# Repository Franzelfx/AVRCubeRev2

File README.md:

# AVR-Cube (Rev2)

**A coin-cell powered electronic dice and two-axis spirit level on an ATtiny24 — seven LEDs, one button, one accelerometer, and a bit-banged I²C bus that shares its pins with the ISP header.**

Shake it and it rolls a number; press the button and the same seven LEDs become a bubble level that follows the tilt of the board. It sleeps after a minute of stillness and wakes on the button, so a CR2032 lasts a long time. Designed as an easy, satisfying through-hole soldering kit: 25 parts, all on one side.

https://user-images.githubusercontent.com/38862049/217531555-265ecb9a-27d7-4d04-bca4-034f5620d8f7.mov

---

## Contents

- [How it works](#how-it-works)
- [Hardware](#hardware)
- [Firmware](#firmware)
- [Building and flashing](#building-and-flashing)
- [Repository layout](#repository-layout)
- [Status and known limitations](#status-and-known-limitations)
- [Author](#author)
- [License](#license)

---

## How it works

The whole device is one state machine driven by two interrupts: a 1 ms timer tick that counts idle time, and the button on `INT0`.

```mermaid
stateDiagram-v2
    [*] --> Calibrate : battery inserted / wake from sleep
    Calibrate --> SpiritLevel : all LEDs → "1" → sensor check ✓ → "2" → offset averaged → ✓
    Calibrate --> Sleep : sensor not answering (✗ shown for 60 s)

    SpiritLevel --> Dice : button
    Dice --> SpiritLevel : button

    state Dice {
        [*] --> Waiting
        Waiting --> Rolling : tilt changes by > 25°
        Rolling --> Waiting : 5 fast + 5 slowing steps, last number stays lit
    }

    SpiritLevel --> Sleep : 60 s without motion
    Dice --> Sleep : 60 s without motion
    SpiritLevel --> Sleep : button held 3 s
    Dice --> Sleep : button held 3 s
    Sleep --> Calibrate : button
```

**Calibration** runs on every wake-up: it lights all LEDs (a visual LED test), reads the accelerometer's `WHO_AM_I` register over I²C, and averages ten samples to get the resting offset on each axis. That offset is what makes the spirit level read "flat" wherever the board happens to sit when powered on — there is no absolute calibration.

**Spirit level** reads X/Y/Z acceleration, subtracts the offset, and converts the X and Y components into roll and pitch angles with `atan(axis / z_offset)`. Within ±1° of level only the centre LED is lit; otherwise the LEDs on the side that is *down* light up — a whole edge if the tilt is along one axis, a single corner if it's diagonal.

**Dice** waits until the angle changes by more than 25° between two readings (a shake or a tilt), then rolls: five numbers at 100 ms, then five more with the delay growing by 100 ms each step, so the animation visibly slows down and settles. The random generator is seeded from the millisecond counter, so the result depends on exactly when you shook it.

**Sleep** puts the accelerometer in standby, switches every I/O pin to input, and enters `SLEEP_MODE_PWR_DOWN` — a few µA. Holding the button lights the LEDs 1…6 as a countdown; at 3 s it sleeps immediately.

## Hardware

| | |
|---|---|
| MCU | Microchip **ATtiny24** (DIP-14, 2 KB flash) at 8 MHz internal RC — the ATtiny84 is a drop-in alternative with more flash |
| Sensor | NXP **MMA8653FC** 3-axis accelerometer (DFN-10), I²C address `0x1D`, ±2 g, 8-bit fast-read mode |
| Display | 7 × 5 mm LEDs in the classic dice pattern, 100 Ω series resistors |
| Input | 6 mm tactile switch on `INT0` |
| Power | CR2032 in a Keystone 106 holder, 3 V direct — no regulator |
| Programming | 2×3 ISP header; the same pins carry the sensor's I²C bus |
| Board | 2-layer, single-sided assembly, KiCad 6 sources in [PCB/](PCB/), Gerbers in [PCB/Gerber/Rev26.09.22/](PCB/Gerber/Rev26.09.22/) |

### LED layout and pin map

```
        D1 ●     ● D2            D1  PA0     D5  PA5 (also MISO)
                                 D2  PA1     D6  PA7
        D3 ●  ●  ● D5            D3  PA2     D7  PB1
              D4                 D4  PA3

        D6 ●     ● D7            SW1  PB2 / INT0   (pull-up, active low)
                                 SCL  PA4 = SCK    (bit-banged, no USI)
   1 → D4   2 → D3 D5            SDA  PA6 = MOSI
   3 → D1 D4 D7   4 → corners    TP101 PB0 (spare, pulled up)
   5 → corners + D4   6 → all but D4
```

Sharing `SCK`/`MOSI` with `SCL`/`SDA` is what keeps the part count down: no dedicated I²C header, and the sensor doesn't mind the ISP traffic because the firmware drives the bus in software and the sensor ignores anything without a valid start condition addressed to it. `D5` sits on `MISO` and flickers while programming — harmless.

### Bill of materials

| Ref | Qty | Part | Footprint |
|---|:---:|---|---|
| U1 | 1 | ATtiny24-20PU (or ATtiny84) | DIP-14 |
| U2 | 1 | MMA8653FCR1 | DFN-10 2×2 mm — the only SMD part |
| D1–D7 | 7 | LED 5 mm | THT |
| R1–R7 | 7 | 100 Ω | axial 0207 |
| C1–C3 | 3 | 100 nF | 0603 |
| C4–C5 | 2 | 1 µF | 0603 |
| SW1 | 1 | tactile switch 6 mm | THT |
| BT1 | 1 | CR2032 holder, Keystone 106 | THT |
| J2 | 1 | pin header 2×3, 2.54 mm | THT |

The schematic ([PCB/avrCubeRev2.kicad_sch](PCB/avrCubeRev2.kicad_sch)) is the authoritative BOM; datasheets for every active part are in [Documentation/](Documentation/).

## Firmware

Everything lives in [AvrCubeV2Code/src/main.cpp](AvrCubeV2Code/src/main.cpp) and [main.hpp](AvrCubeV2Code/src/main.hpp) — bare-metal AVR C++ with no Arduino API calls, built with the PlatformIO `atmelavr` toolchain. Doxygen comments on every function; the generated reference is in [Documentation/Doxygen/documentation.pdf](Documentation/Doxygen/documentation.pdf).

Things worth knowing before you change it:

- **I²C is bit-banged** (`start()`, `stop()`, `tx()`, `rx()`) at ~100 kHz using the internal pull-ups — the ATtiny24's USI is not used so the pins can double as ISP. Interrupts are disabled during each register transaction.
- **The 1 ms tick** is Timer0 in CTC mode (prescaler 64, `OCR0A = 124` at 8 MHz). It only increments `counter`; `main()` compares it against `SLEEP_THRESHOLD` and any detected motion resets it.
- **Mode switching** is done by parity of `button_pressed`: the ISR increments it and re-enters `main()`, which re-initialises the peripherals and picks the branch. Odd = dice, even = spirit level; calibration leaves it at 2, so the device starts in level mode.
- **All tunables are `#define`s** at the top of `main.hpp`: sleep timeout, shake threshold, dice animation timing, level dead-band, hold-to-sleep time.

## Building and flashing

Requirements: [PlatformIO](https://platformio.org/) (CLI or VS Code extension) and an ISP programmer — an Arduino running *ArduinoISP* works, that's what `flashCommand.txt` assumes.

```bash
cd AvrCubeV2Code
pio run -e attiny24            # or -e attiny84
```

Flash with avrdude, setting the fuses for the internal 8 MHz oscillator with `CKDIV8` cleared (`lfuse 0xE2`); the default `hfuse 0xDF` keeps `RESET` usable so the chip stays re-programmable:

```bash
avrdude -p t24 -c avrisp -b 19200 -P /dev/ttyUSB0 \
  -U flash:w:.pio/build/attiny24/firmware.hex \
  -U lfuse:w:0xe2:m -U hfuse:w:0xdf:m -U efuse:w:0xff:m
```

Insert the coin cell after programming. The board should light all seven LEDs, show `1`, then a tick mark (✓) if the accelerometer answered, show `2` while it averages the offset, and a tick again — then it's in spirit-level mode. A cross (✗) after `1` means the I²C link to the sensor is broken; check the DFN-10 solder joints.

## Repository layout

```
AvrCubeV2Code/         PlatformIO project
  src/main.cpp, main.hpp   the whole firmware
  platformio.ini           attiny24 and attiny84 environments
  flashCommand.txt         avrdude invocation with fuse settings
  Doxygen/Doxyfile         doc generator config
PCB/                   KiCad 6 project (schematic, layout, footprint table)
  Gerber/Rev26.09.22/      latest production files (also Rev09.22, Rev1.0)
Documentation/         datasheets (ATtiny24, MMA8653FC, LED) and the Doxygen PDF
Resources/             board render, demo video, KiCad battery-holder footprints
```

## Status and known limitations

The Rev2 board is built, tested and works as shown in the video. Things left open in the firmware:

- **Angle maths is an approximation.** Roll and pitch use `atan(x / z_offset)` with the *calibrated* Z as the fixed reference rather than `atan2(x, sqrt(y²+z²))`. It's accurate near level and increasingly off beyond ~45°, which is fine for a bubble level but not for measuring angles. The NXP app note AN3461 has the exact formulas; the code comment already points at it.
- **Motion detection is rough.** `motionDetected()` compares the angle *gradient* to the threshold without `abs()`, so only changes in the positive direction trigger — and `getGradient()` keeps a single static previous value shared between the roll and pitch calls, so each "gradient" is really roll-minus-pitch of consecutive reads. Shaking still trips it reliably, which is all the dice needs, but it should be two independent deltas with `abs()`.
- **Offset lives in RAM.** Calibration repeats on every wake-up rather than storing the offset in the sensor's own offset registers (`OFF_X/Y/Z`), which the MMA8653FC supports.
- **Mode switching re-enters `main()` from the ISR**, which is a stack-growing trick rather than a clean state variable. It works because the device sleeps or is power-cycled long before the stack matters, but it's the first thing to refactor.
- **Flash is tight on the ATtiny24.** Float `atan` plus `rand` fits, but there is little room left; the ATtiny84 environment exists for that reason.

## Author

Fabian Franz, 2022.

## License

Firmware, schematic and board layout: [MIT](LICENSE). Datasheets in `Documentation/` belong to their respective manufacturers.

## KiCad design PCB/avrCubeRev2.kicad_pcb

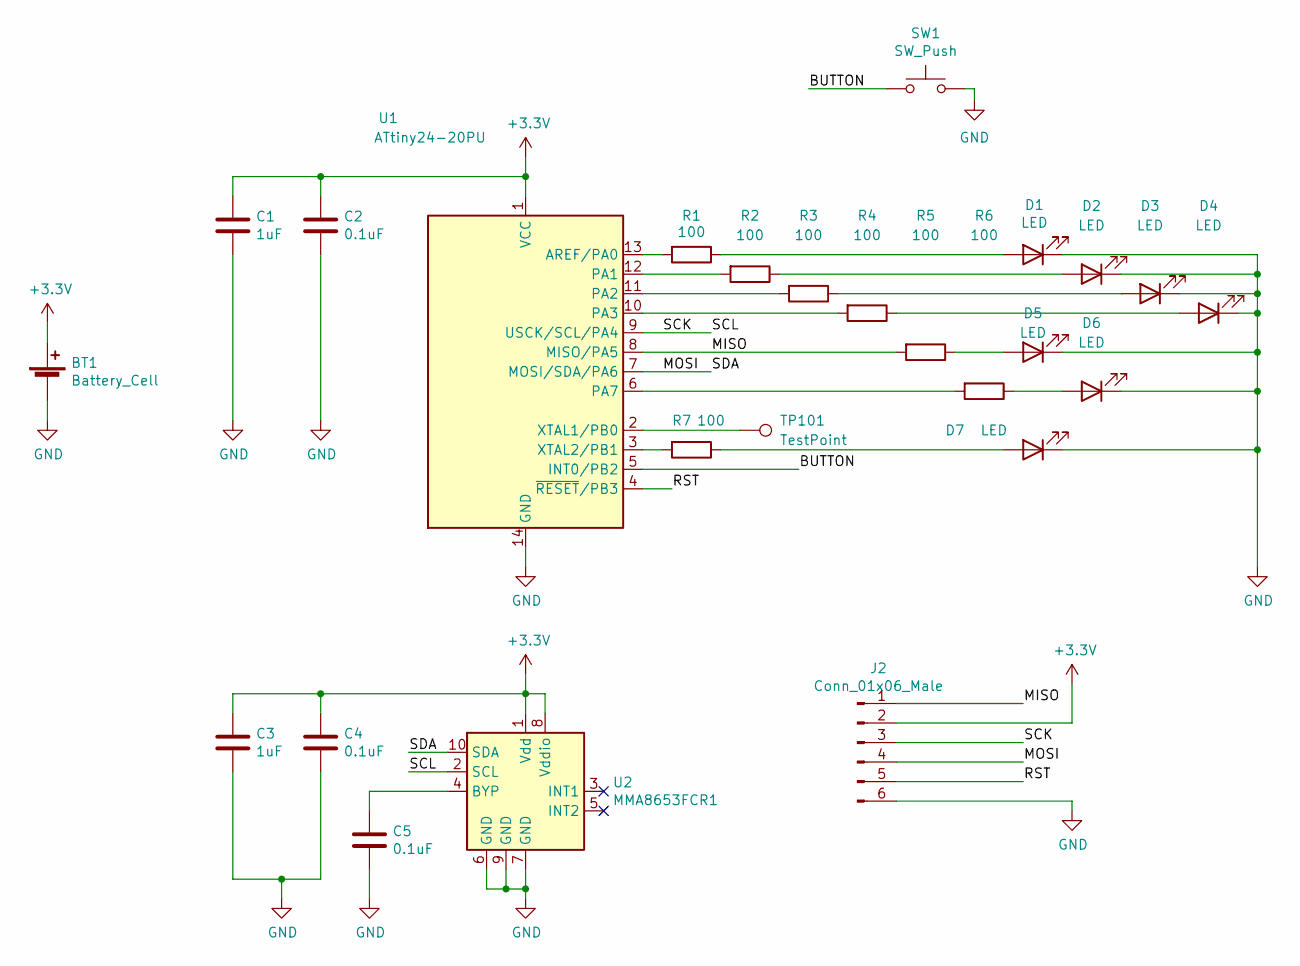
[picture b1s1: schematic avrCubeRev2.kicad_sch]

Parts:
BT1: Battery_Cell; BatteryHolder_Keystone_106_1x20mm
C1, C3: 1uF; C_0603
C2, C4, C5: 0.1uF; C_0603
D1, D2, D3, D4, D5, D6, D7: LED; LED_D5.0mm
J2: Conn_01x06_Male; Pin_Header_Straight_2x03_Pitch2.54mm
R1, R2, R3, R4, R5, R6, R7: 100; R_Axial_DIN0207_L6.3mm_D2.5mm_P10.16mm_Horizontal
SW1: SW_Push; SW_PUSH_6mm_h4.3mm
TP101: TestPoint; TestPoint_2Pads_Pitch2.54mm_Drill0.8mm
U1: ATtiny24-20PU; DIP-14_W7.62mm_LongPads
U2: MMA8653FCR1; DFN-10_2x2mm_Pitch0.4mm

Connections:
+3V3: BT1.1 (+), C1.1, C2.1, C3.1, C4.1, J2.2, U1.1 (VCC), U2.1 (Vdd), U2.8 (Vddio)
/BUTTON: SW1.1, U1.5 (INT0/PB2)
/MISO: J2.1, R5.2, U1.8 (MISO/PA5)
/MOSI: J2.4, U1.7 (MOSI/SDA/PA6), U2.10 (SDA)
/RST: J2.5, U1.4 (~RESET/PB3)
/SCK: J2.3, U1.9 (USCK/SCL/PA4), U2.2 (SCL)
GND: BT1.2 (-), C1.2, C2.2, C3.2, C4.2, C5.2, D1.1 (K), D2.1 (K), D3.1 (K), D4.1 (K), D5.1 (K), D6.1 (K), D7.1 (K), J2.6, SW1.2, TP101.2, U1.14 (GND), U2.6 (GND), U2.7 (GND), U2.9 (GND)
unnamed: C5.1, U2.4 (BYP)
unnamed: D1.2 (A), R1.1
unnamed: D2.2 (A), R2.1
unnamed: D3.2 (A), R3.1
unnamed: D4.2 (A), R4.1
unnamed: D5.2 (A), R5.1
unnamed: D6.2 (A), R6.1
unnamed: D7.2 (A), R7.1
unnamed: R1.2, U1.13 (AREF/PA0)
unnamed: R2.2, U1.12 (PA1)
unnamed: R3.2, U1.11 (PA2)
unnamed: R4.2, U1.10 (PA3)
unnamed: R6.2, U1.6 (PA7)
unnamed: R7.2, U1.3 (XTAL2/PB1)
unnamed: TP101.1, U1.2 (XTAL1/PB0)

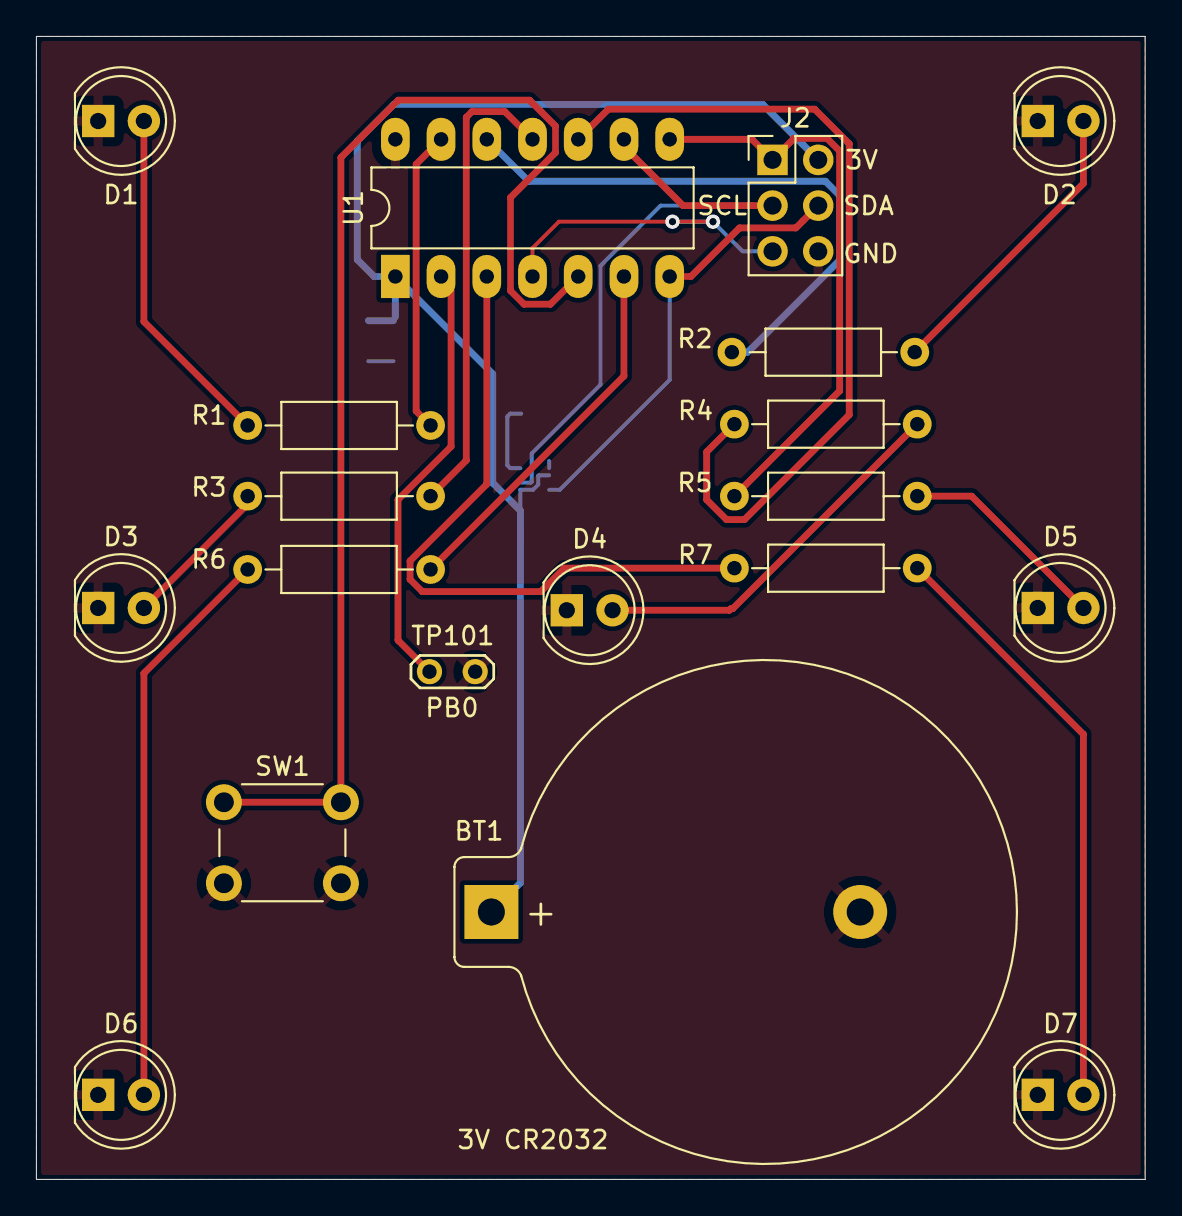
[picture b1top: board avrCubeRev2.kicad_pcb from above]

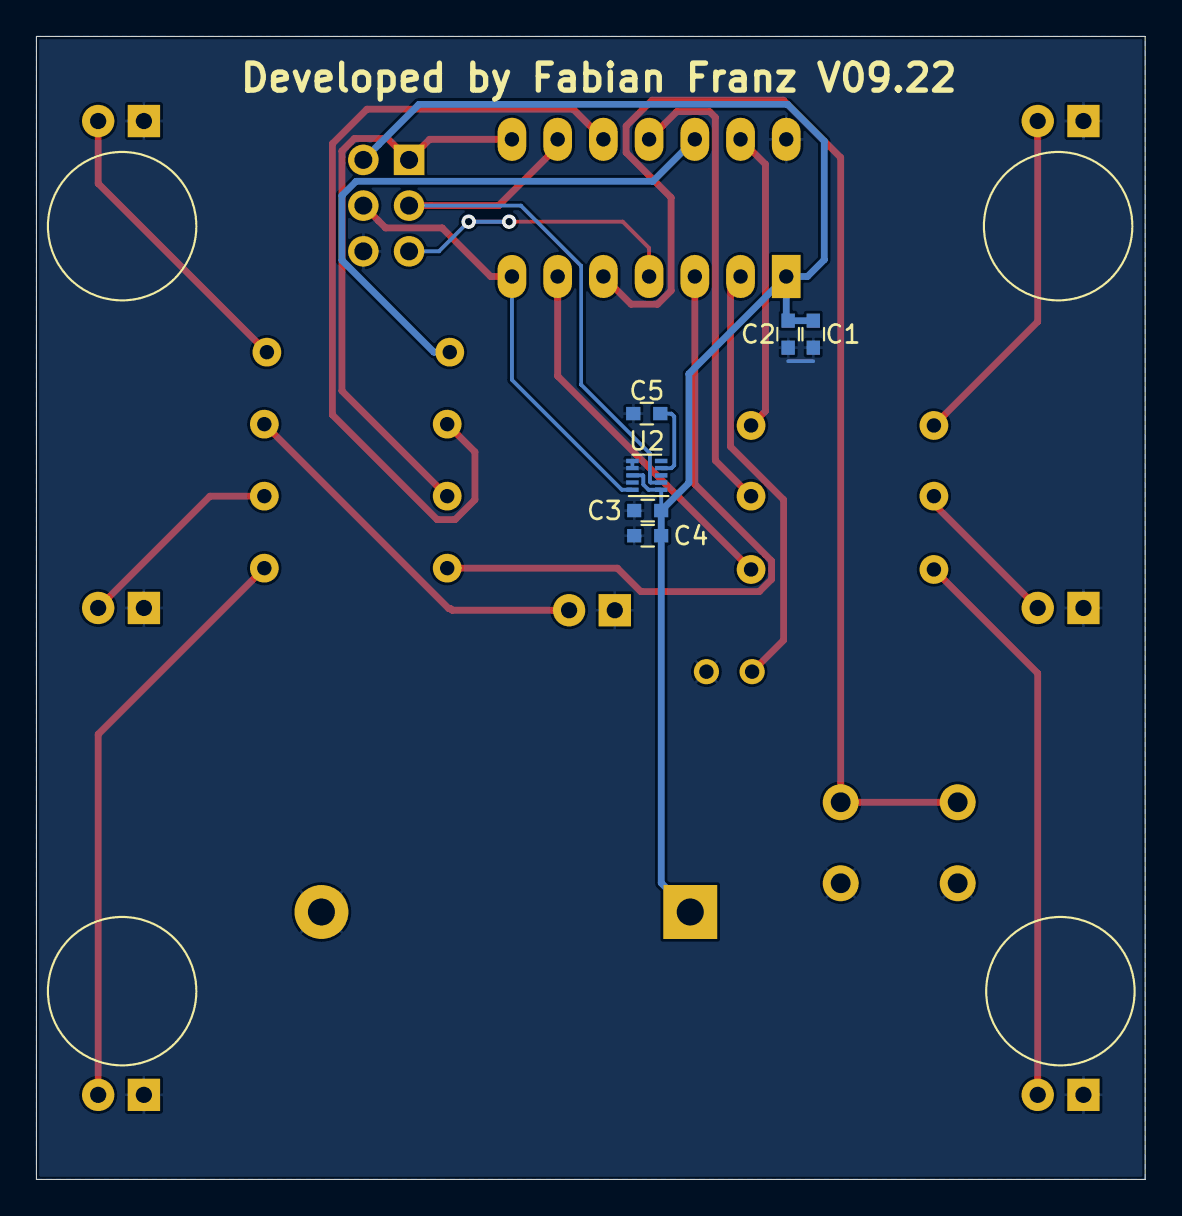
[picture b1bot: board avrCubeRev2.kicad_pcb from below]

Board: 2 copper layers, 61.6 x 63.5 mm, 25 parts (6 on the bottom side), 22 nets.

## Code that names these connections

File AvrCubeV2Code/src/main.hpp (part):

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#define F_CPU 8000000
#define __DELAY_BACKWARD_COMPATIBLE__
// Defines for the button pin
#define BUTTON PB2
// Defines for the connected LEDs
#define D1 PA0
#define D2 PA1
#define D3 PA2
#define D4 PA3
#define D5 PA5
#define D6 PA7
#define D7 PB1
// Defines for the SPI interface.
#define SCK PA4
#define MISO PA5
#define MOSI PA6
// Defines for the I2C interface (no hardware interface).
#define SCL PA4
#define SDA PA6
// Defines for unconnected pins
#define UNCONNECTED PB0

// General defines
#define OUTPUT 0
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
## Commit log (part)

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2022-08-25 Read acceleration on x,y,z done
2022-08-25 Complete program with 8Bit precision
2022-08-26 Final working code, not reviewed yet.
2022-08-26 Introduced acceleration and forced shutdown
2022-09-15 Exported Gerber, Added Comments, Added Doxygen
2022-09-15 Improved motionDetected()
2022-09-16 Final Version 16.09.2022
2022-11-26 FINAL version
2023-02-08 REMOVED Bills
2023-02-08 EDIT readme
2023-02-08 REMOVED latex sources

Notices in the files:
AvrCubeV2Code/src/main.hpp:
@copyright Copyright (c) 2022
